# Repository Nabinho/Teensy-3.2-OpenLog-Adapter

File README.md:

# Teensy-3.2-OpenLog-Adapter
Adapter PCB to Teensy 3.2 Board with OpenLog module

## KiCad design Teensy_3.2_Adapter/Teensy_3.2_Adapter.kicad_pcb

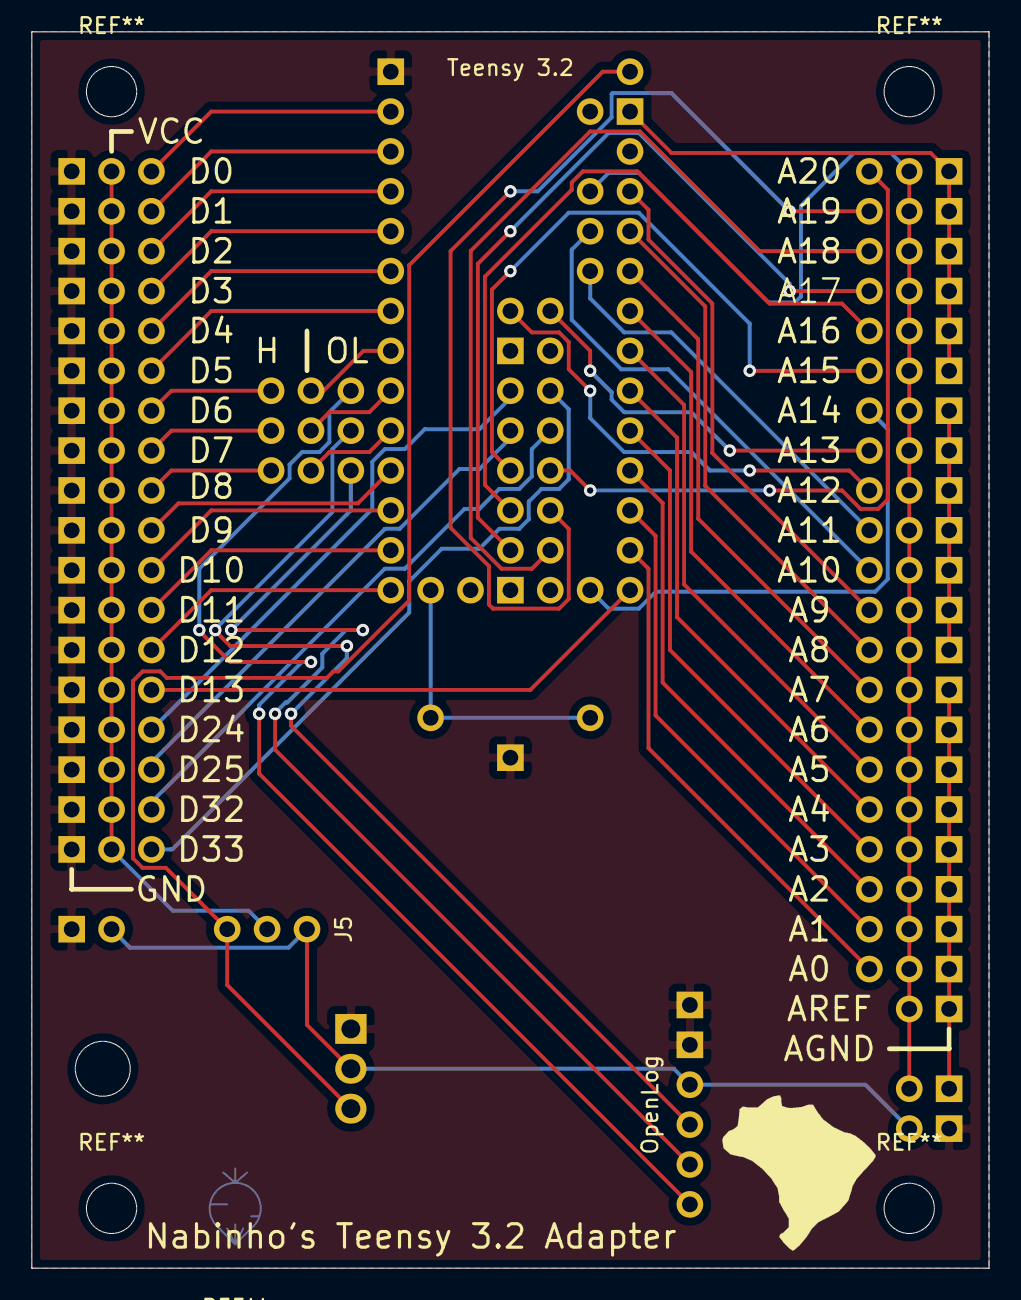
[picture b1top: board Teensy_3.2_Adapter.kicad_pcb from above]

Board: 2 copper layers, 61.0 x 78.7 mm, 13 parts (0 on the bottom side), 52 nets.

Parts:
BT1: Battery_Cell; CR2032_Vertical
C1: CP; PinHeader_1x02_P2.54mm_Vertical
J1: Conn_03x21; Analog_Header_Teensy_3.2_Adapter
J2: Conn_03x18; Digital_Header_Teensy_3.2_Adapter
J3: Conn_01x02; PinHeader_1x02_P2.54mm_Vertical_3
J4: Conn_01x02; PinHeader_1x02_P2.54mm_Vertical_2
J5, J6, J7, J8: Conn_01x03; PinHeader_1x03_P2.54mm_Vertical_2
U1: Teensy3.2; Teensy_3.2
U2: LD1117S33TR_SOT223; TO-220F-3_Horizontal_TabUp
U3: OpenLog; Open_Log

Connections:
0: J2.1, U1.2
1: J2.2, U1.3
2: J2.3, U1.4
3: J2.4, U1.5
4: J2.5, U1.6
5: J2.6, U1.7
6: J6.2, U1.8
6_H: J2.7, J6.3
6_L: J6.1, U3.6
7: J7.2, U1.9
7_H: J2.8, J7.3
7_L: J7.1, U3.4
8: J8.2, U1.10
8_H: J2.9, J8.3
8_L: J8.1, U3.5
9: J2.10, U1.11
10: J2.11, U1.12
11: J2.12, U1.13
12: J2.13, U1.14
13: J2.14, U1.20
24: J2.15, U1.52
25: J2.16, U1.51
32: J2.17, U1.44
33: J2.18, U1.43
A0: J1.1, U1.21
A1: J1.2, U1.22
A2: J1.3, U1.23
A3: J1.4, U1.24
A4: J1.5, U1.25
A5: J1.6, U1.26
A6: J1.7, U1.27
A7: J1.8, U1.28
A8: J1.9, U1.29
A9: J1.10, U1.30
A10: J1.11, U1.36
A11: J1.12, U1.37
A12: J1.13, U1.54
A13: J1.14, U1.41
A14: J1.15, U1.19
A15: J1.16, U1.50
A16: J1.17, U1.49
A17: J1.18, U1.48
A18: J1.19, U1.47
A19: J1.20, U1.46
A20: J1.21, U1.45
AGND: J1.23, J3.2, U1.32
AREF: J1.22, J4.2, U1.35
GND: BT1.2, C1.2, J2.20, J3.1, U1.1, U1.17, U1.53, U2.1, U3.1, U3.2
VBAT: BT1.1, U1.15
VCC: J2.19, J5.2
VIN: J5.3, U1.33, U2.3
VOUT: C1.1, J4.1, J5.1, U2.2, U3.3
